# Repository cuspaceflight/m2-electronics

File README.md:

# Martlet 2 Flight Computers

This repository contains the schematics, PCB designs and firmware for the
various electronic systems onboard Martlet 2.

## M2FC: Flight Computer
This PCB records sensor data to onboard storage and determines when to fire
pyrotechnic channels for staging and parachute release.

## M2R: Radio
This PCB receives GPS signals and transmits rocket telemetry (lat, lng, alt, 
max alt) over a satellite radio and 70cm radio link.

## Radio Link M2RL
Communicate between two M2FCs

## Firmware
### ChibiOS Instructions

```bash
$ git submodule update --init
$ cd ChibiOS/ext
$ unzip fatfs-0.9-patched.zip
$ cd ../os/various/fatfs_bindings
$ sed -i '/extern SDCDriver SDCD1;/d' fatfs_diskio.c
```

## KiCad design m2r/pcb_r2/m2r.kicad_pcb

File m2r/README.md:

# Martlet 2 Radio Board

This PCB transmits rocket telemetry (lat, lng, alt, max alt) over a satellite
radio and 70cm radio link.

The satellite radio uses a RockBLOCK Iridium modem. The 70cm link will use an
NTX2b from Radiometrix with a standard 1/4 wave antenna, in a similar setup to
the usual HAB case.

There's some possibility for clever radio modes and coding to be used, but it
will depend on how much time is available.

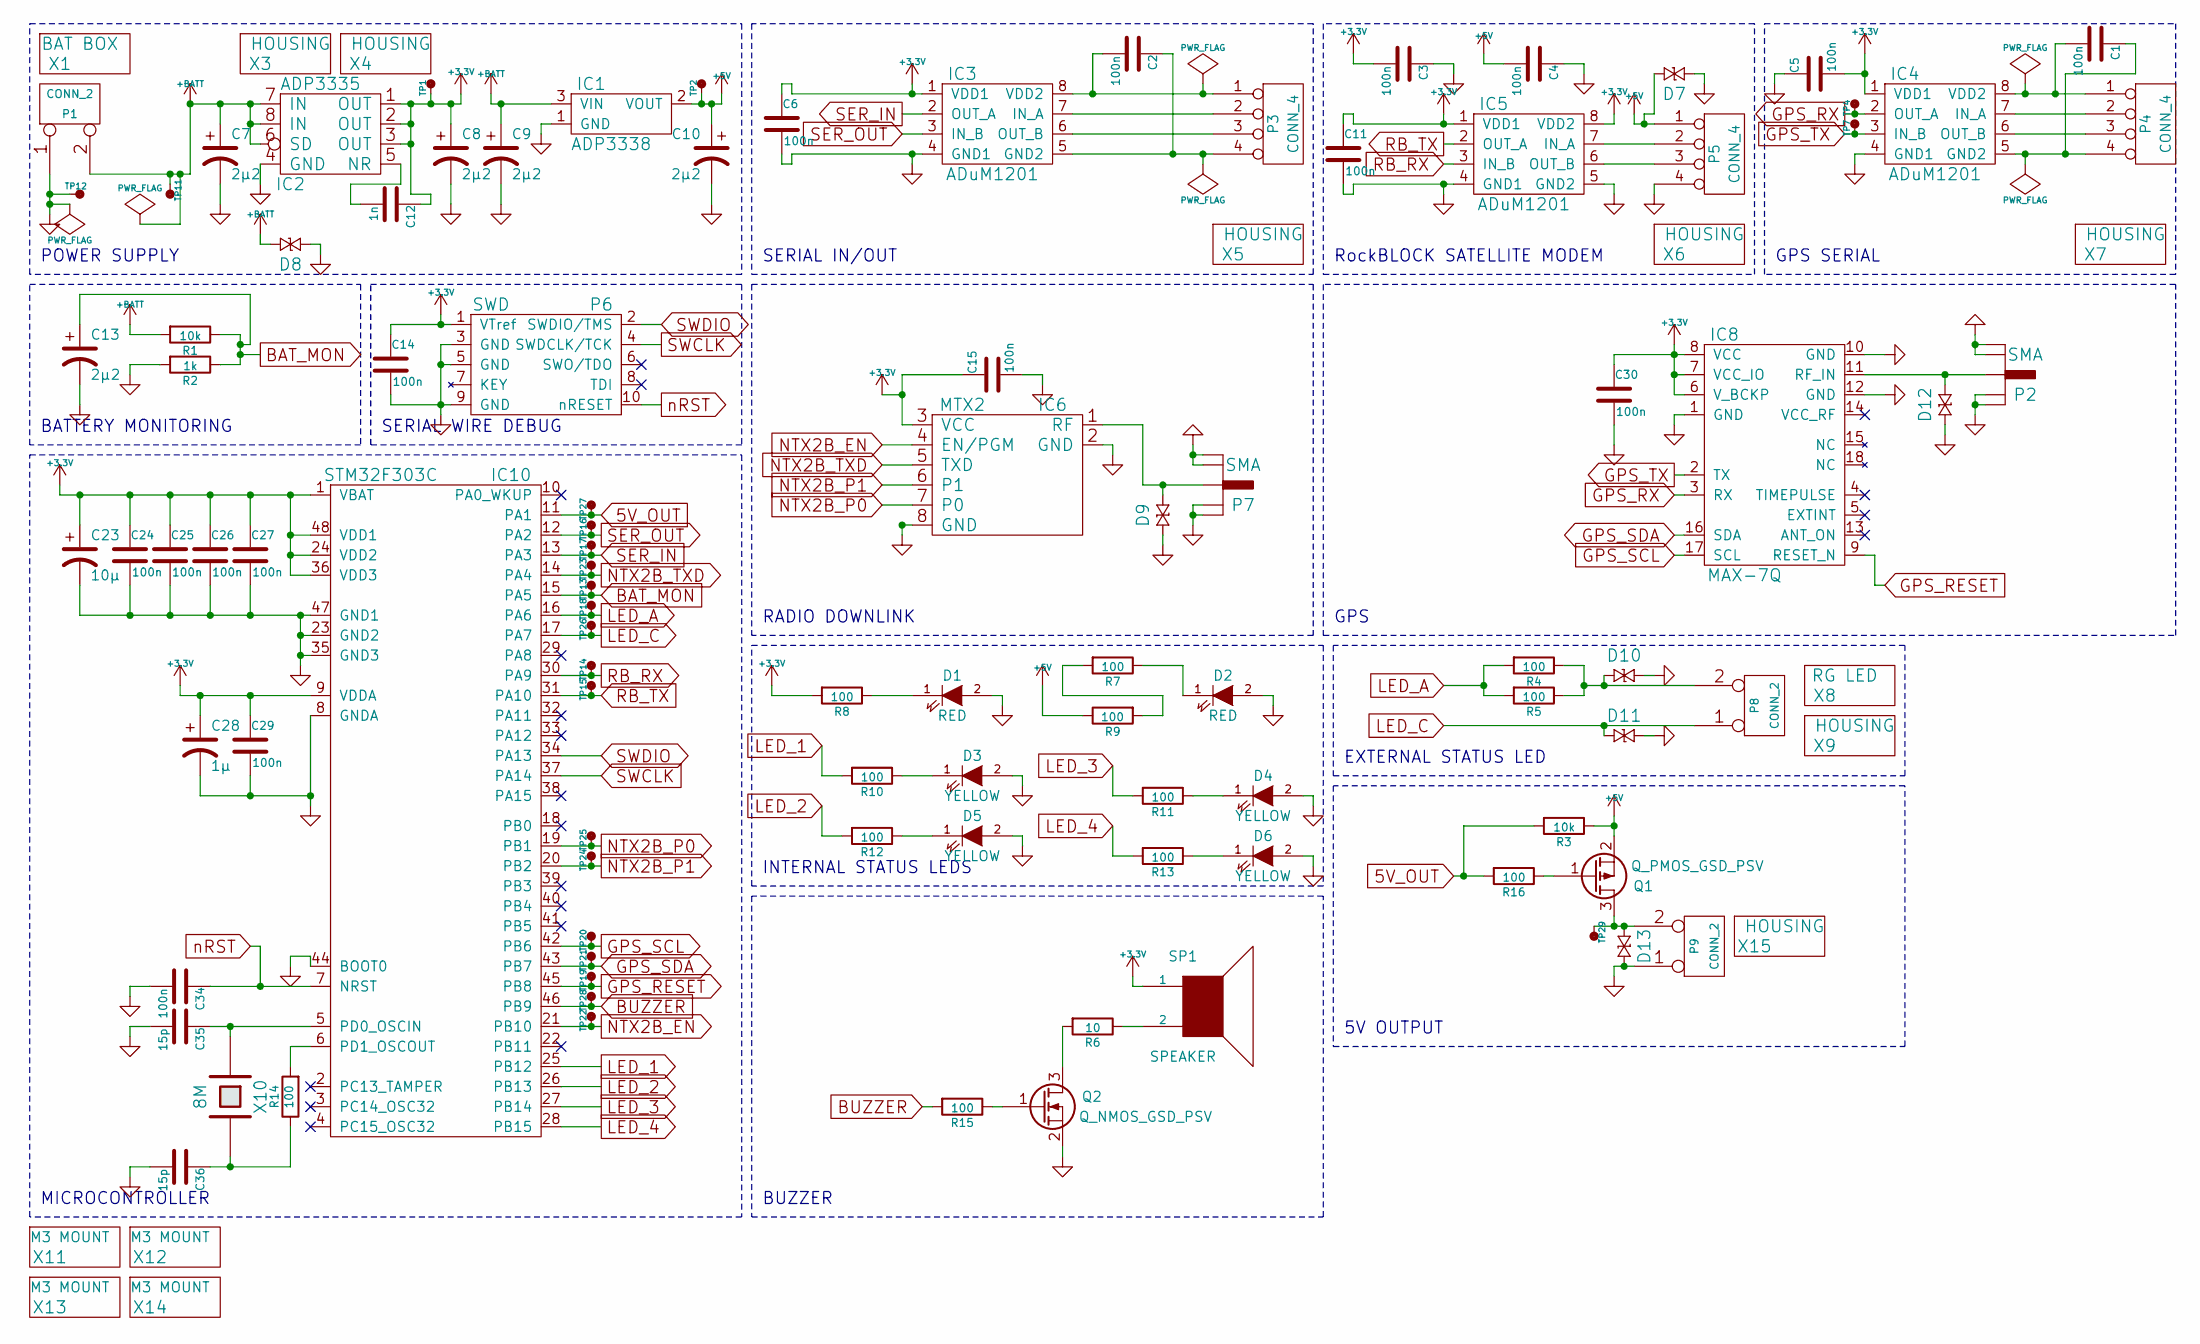
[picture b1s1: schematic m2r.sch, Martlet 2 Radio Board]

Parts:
C1, C2, C3, C4, C5, C6, C11, C14, C15, C24, C25, C26, C27, C29, C30, C34: 100n; C0603; Farnell 1759037
C7, C8, C9, C10, C13: 2µ2; C0603; Farnell 2320817
C12: 1n; C0603; Farnell 1759088
C23: 10µ; C0603; Farnell 2333026
C28: 1µ; C0603; Farnell 1658211
C35, C36: 15p; C0603; Farnell 1759055
D1, D2: RED; LED0603; Farnell 2290329
D3, D4, D5, D6: YELLOW; LED0603; Farnell 2290330
D7, D8, D9, D10, D11, D12, D13: CGA0402MLC-12G; R0402; Farnell 2368169
IC1: ADP3338; SOT223; Farnell 1651284
IC2: ADP3335; MSOP8; Farnell 2067775
IC3, IC4, IC5: ADuM1201; SOIC8; Farnell 1078200
IC6: MTX2
IC8: MAX-7Q
IC10: STM32F303C; LQFP48; Farnell 2333361
P1, P8, P9: CONN_2; S02B-PASK-2; Farnell 1830747
P2, P7: SMA; SMA-142-0701-801; Farnell 1608592
P3, P4, P5: CONN_4; S04B-PASK-2
P6: SWD; FTSH-105-01-F-D-K; Farnell 2308436
Q1: Q_PMOS_GSD_PSV; SOT-23; Farnell 1894738
Q2: Q_NMOS_GSD_PSV; SOT-23; Farnell 1510761
R1, R3: 10k; R0603; Farnell 2332016
R2: 1k; R0603; Farnell 2331727
R4, R5, R7, R8, R9, R10, R11, R12, R13, R14, R15, R16: 100; R0603; Farnell 2331989
R6: 10; R0603; Farnell 2331975
SP1: SPEAKER; ABI-042-RC; Farnell 1827949
TP1, TP2, TP4, TP7, TP11, TP12, TP13, TP14, TP15, TP16, TP17, TP18, TP19, TP20, TP21, TP22, TP23, TP24, TP25, TP26, TP27, TP28, TP29: TESTPAD
X1: BAT BOX; Farnell BT01732
X3, X4, X9, X15: HOUSING; Farnell 1830726
X5, X6, X7: HOUSING; Farnell 1830729
X8: RG LED; Farnell 1142488
X10: 8M; XTAL50x32; Farnell 2101329
X11, X12, X13, X14: M3 MOUNT; M3_MOUNT

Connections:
5V_OUT: IC10.11 (PA1), R3.2, R16.2, TP27.1
+3V3: C3.2, C5.2, C6.1, C8.1, C11.1, C12.1, C14.1, C15.1, C23.1, C24.1, C25.1, C26.1, C27.1, C28.1, C29.1, C30.1, IC2.1 (OUT), IC2.2 (OUT), IC2.3 (OUT), IC3.1 (VDD1), IC4.1 (VDD1), IC5.1 (VDD1), IC5.8 (VDD2), IC6.3 (VCC), IC8.6 (V_BCKP), IC8.7 (VCC_IO), IC8.8 (VCC), IC10.1 (VBAT), IC10.9 (VDDA), IC10.24 (VDD2), IC10.36 (VDD3), IC10.48 (VDD1), P6.1 (VTref), R8.2, SP1.1, TP1.1
+5V: C4.2, C10.1, D7.1, IC1.2 (VOUT), P5.1, Q1.2 (S), R3.1, R9.1, TP2.1
+BATT: C7.1, C9.1, D8.1, IC1.3 (VIN), IC2.6 (SD), IC2.7 (IN), IC2.8 (IN), P1.2 (PM), R1.2, TP11.1
BAT_MON: C13.1, IC10.15 (PA5), R1.1, R2.1, TP13.1
BUZZER: IC10.46 (PB9), R15.2, TP28.1
GND: C3.1, C4.1, C5.1, C6.2, C7.2, C8.2, C9.2, C10.2, C11.2, C13.2, C14.2, C15.2, C23.2, C24.2, C25.2, C26.2, C27.2, C28.2, C29.2, C30.2, C34.2, C35.2, C36.2, D1.2 (A), D2.2 (A), D3.2 (A), D4.2 (A), D5.2 (A), D6.2 (A), D7.2, D8.2, D9.2, D10.1, D11.1, D12.2, D13.1, IC1.1 (GND), IC2.4 (GND), IC3.4 (GND1), IC4.4 (GND1), IC5.4 (GND1), IC5.5 (GND2), IC6.2 (GND), IC6.8 (GND), IC8.1 (GND), IC8.10 (GND), IC8.12 (GND), IC10.8 (GNDA), IC10.23 (GND2), IC10.35 (GND3), IC10.44 (BOOT0), IC10.47 (GND1), P1.1, P2.2 (GND), P2.3 (GND), P2.4 (GND), P2.5 (GND), P5.4, P6.3 (GND), P6.5 (GND), P6.9 (GND), P7.2 (GND), P7.3 (GND), P7.4 (GND), P7.5 (GND), P9.1, Q2.2 (S), R2.2, TP12.1
GPS_RESET: IC8.9 (RESET_N), IC10.45 (PB8), TP19.1
GPS_RX: IC4.2 (OUT_A), IC8.3 (RX), TP4.1
GPS_SCL: IC8.17 (SCL), IC10.42 (PB6), TP20.1
GPS_SDA: IC8.16 (SDA), IC10.43 (PB7), TP21.1
GPS_TX: IC4.3 (IN_B), IC8.2 (TX), TP7.1
LED_1: IC10.25 (PB12), R10.2
LED_2: IC10.26 (PB13), R12.2
LED_3: IC10.27 (PB14), R11.2
LED_4: IC10.28 (PB15), R13.2
LED_A: IC10.16 (PA6), R4.2, R5.2, TP18.1
LED_C: D11.2, IC10.17 (PA7), P8.1, TP26.1
NTX2B_EN: IC6.4 (EN/PGM), IC10.21 (PB10), TP22.1
NTX2B_P0: IC6.7 (P0), IC10.19 (PB1), TP25.1
NTX2B_P1: IC6.6 (P1), IC10.20 (PB2), TP24.1
NTX2B_TXD: IC6.5 (TXD), IC10.14 (PA4), TP23.1
unnamed: C1.1, IC4.5 (GND2), P4.4
unnamed: C1.2, IC4.8 (VDD2), P4.1
unnamed: C2.1, IC3.5 (GND2), P3.4
unnamed: C2.2, IC3.8 (VDD2), P3.1
unnamed: C12.2, IC2.5 (NR)
unnamed: C35.1, IC10.5 (PD0_OSCIN), X10.1
unnamed: C36.1, R14.1, X10.2
unnamed: D1.1 (K), R8.1
unnamed: D2.1 (K), R7.1
unnamed: D3.1 (K), R10.1
unnamed: D4.1 (K), R11.1
unnamed: D5.1 (K), R12.1
unnamed: D6.1 (K), R13.1
unnamed: D9.1, IC6.1 (RF), P7.1 (RF)
unnamed: D10.2, P8.2 (PM), R4.1, R5.1
unnamed: D12.1, IC8.11 (RF_IN), P2.1 (RF)
unnamed: D13.2, P9.2 (PM), Q1.3 (D), TP29.1
unnamed: IC3.6 (OUT_B), P3.3
unnamed: IC3.7 (IN_A), P3.2
unnamed: IC4.6 (OUT_B), P4.3
unnamed: IC4.7 (IN_A), P4.2
unnamed: IC5.6 (OUT_B), P5.3
unnamed: IC5.7 (IN_A), P5.2
unnamed: IC10.6 (PD1_OSCOUT), R14.2
unnamed: Q1.1 (G), R16.1
unnamed: Q2.1 (G), R15.1
unnamed: Q2.3 (D), R6.2
unnamed: R6.1, SP1.2
unnamed: R7.2, R9.2
RB_RX: IC5.3 (IN_B), IC10.30 (PA9), TP14.1
RB_TX: IC5.2 (OUT_A), IC10.31 (PA10), TP15.1
SER_IN: IC3.2 (OUT_A), IC10.13 (PA3), TP17.1
SER_OUT: IC3.3 (IN_B), IC10.12 (PA2), TP16.1
SWCLK: IC10.37 (PA14), P6.4 (SWDCLK/TCK)
SWDIO: IC10.34 (PA13), P6.2 (SWDIO/TMS)
nRST: C34.1, IC10.7 (NRST), P6.10 (nRESET)

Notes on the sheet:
POWER SUPPLY
BATTERY MONITORING
SERIAL WIRE DEBUG
SERIAL IN/OUT
RockBLOCK SATELLITE MODEM
RADIO DOWNLINK
GPS
MICROCONTROLLER
EXTERNAL STATUS LED
INTERNAL STATUS LEDS
GPS SERIAL
BUZZER
5V OUTPUT

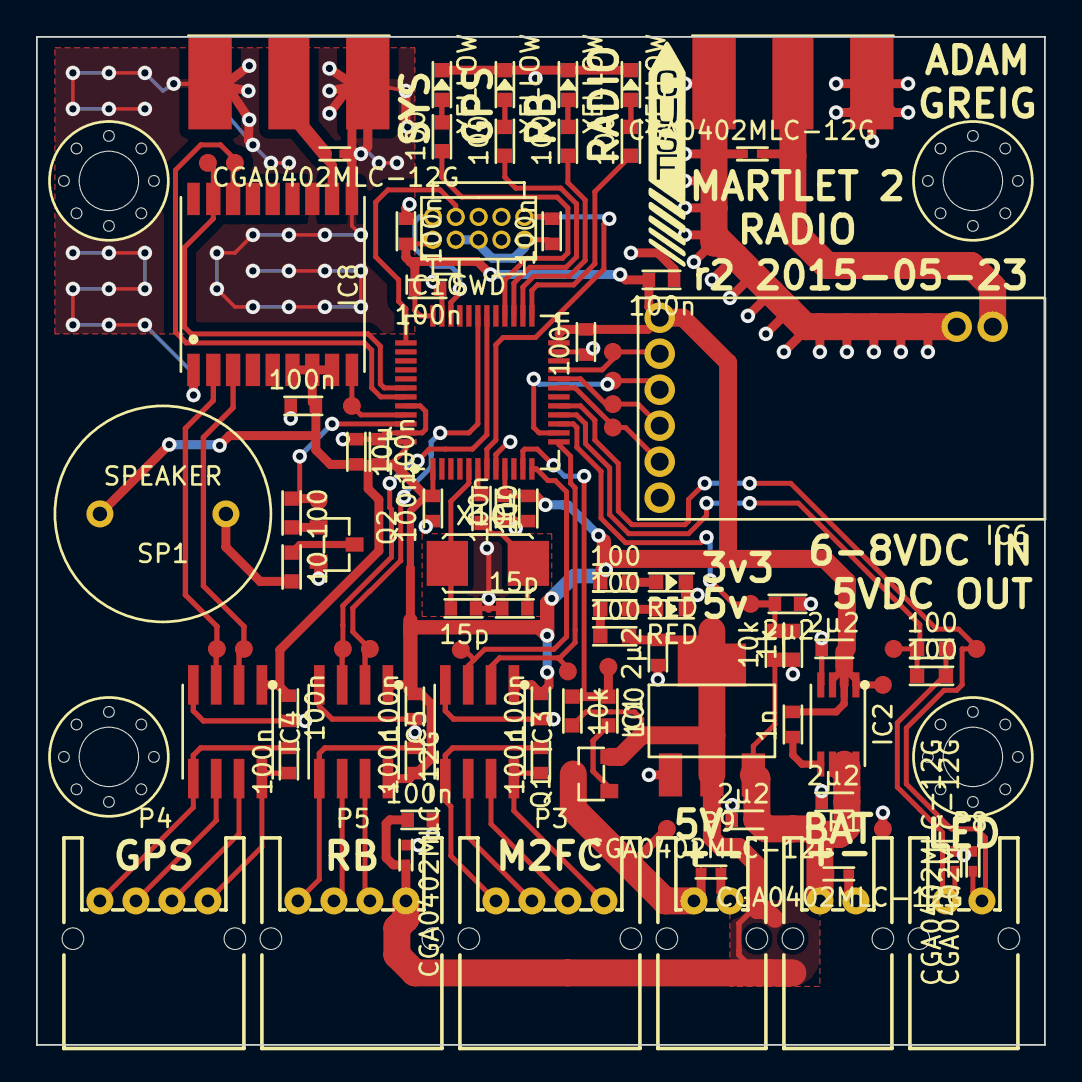
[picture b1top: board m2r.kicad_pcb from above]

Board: 2 copper layers, 56.0 x 56.0 mm, 103 parts (0 on the bottom side), 58 nets.

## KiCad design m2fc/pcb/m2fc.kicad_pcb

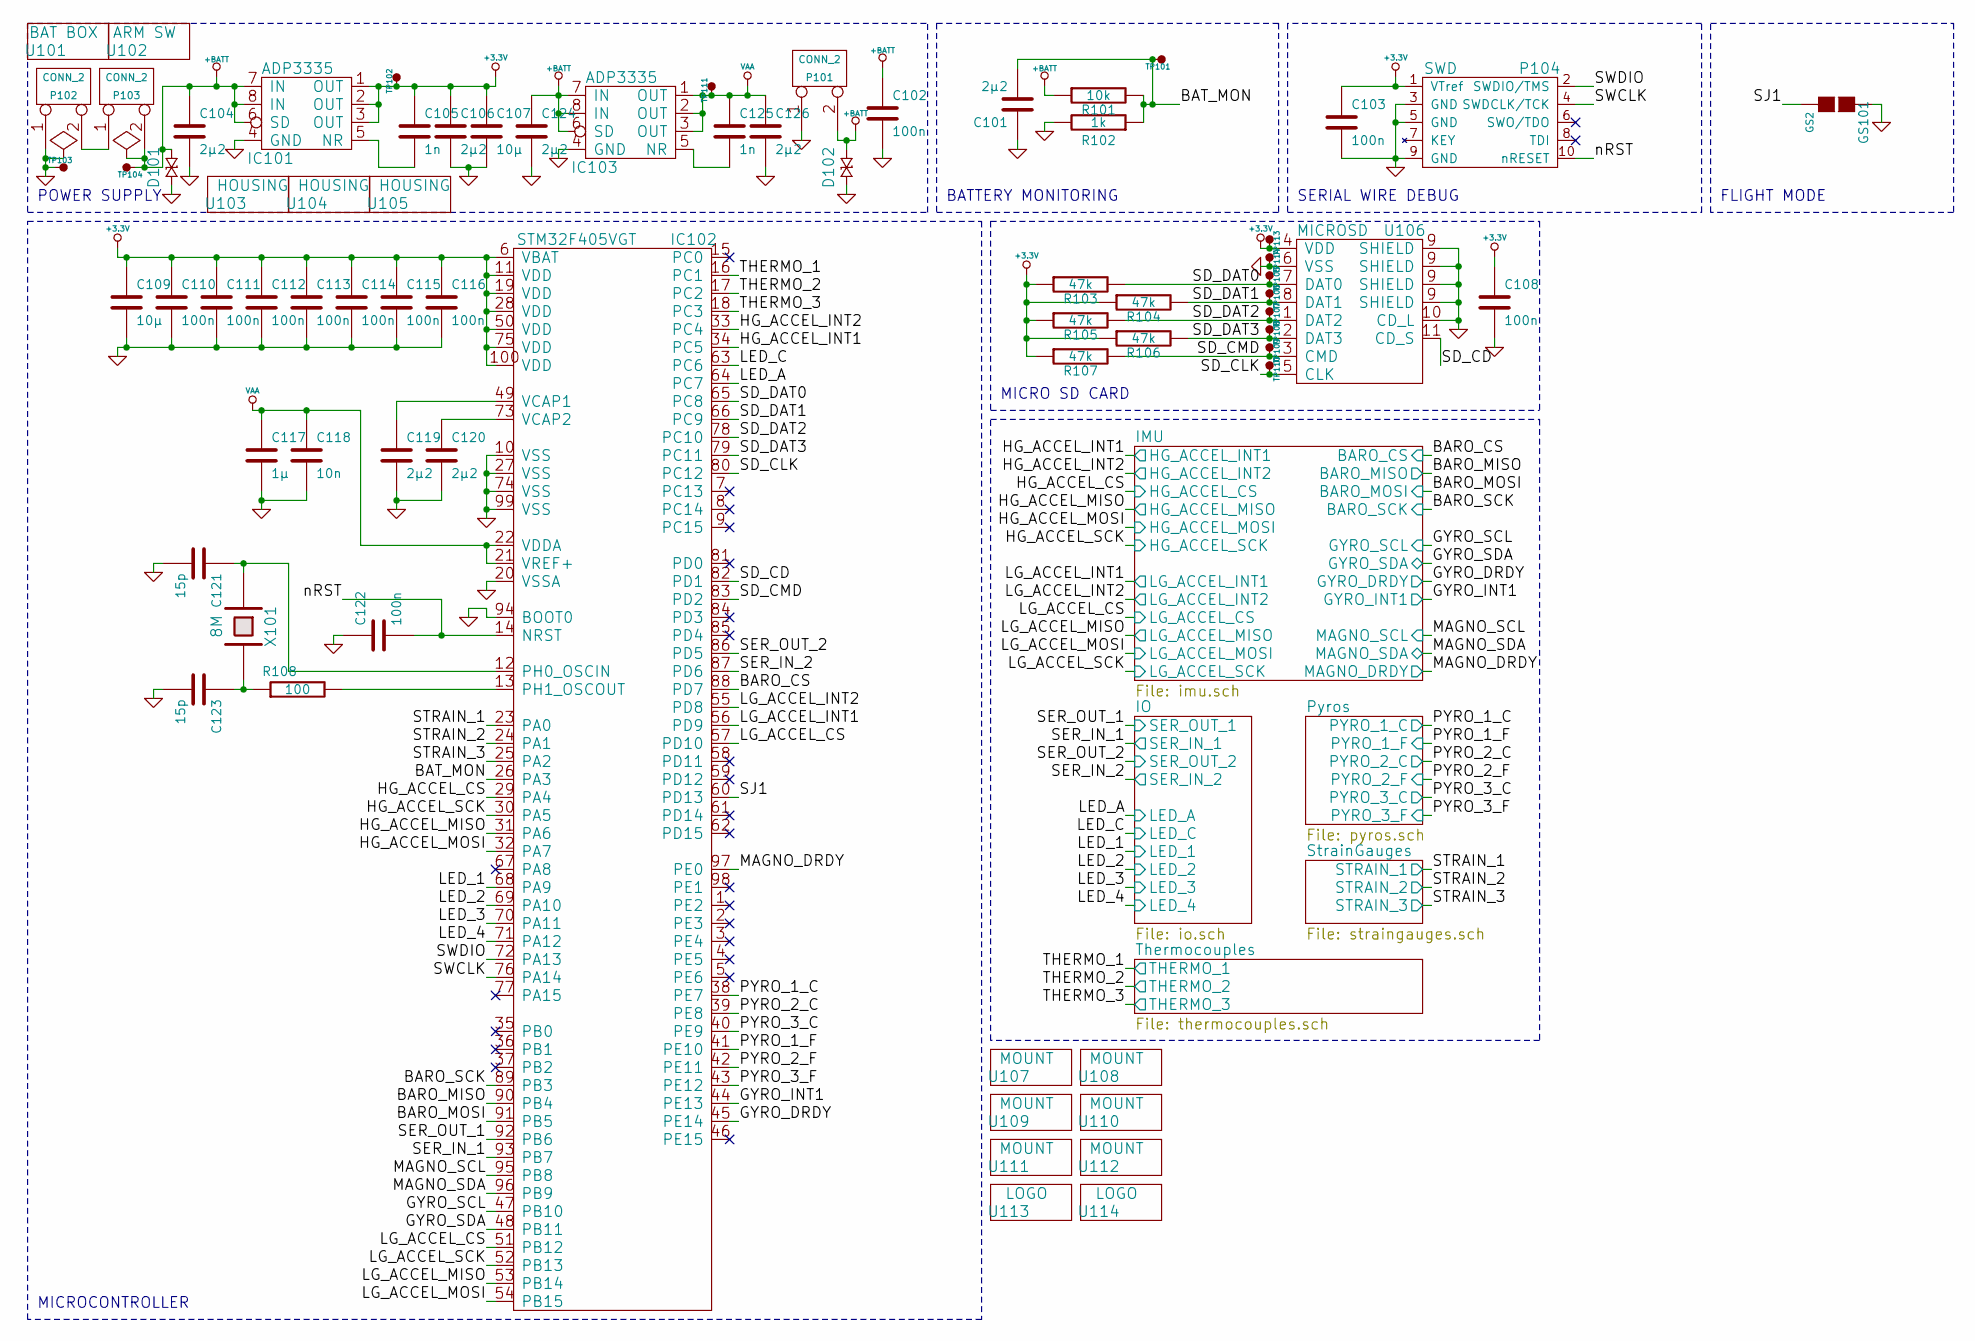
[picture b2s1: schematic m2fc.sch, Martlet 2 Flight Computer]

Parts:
C101, C104, C106, C119, C120, C124, C126: 2µ2; C0603; Farnell 2320817
C102, C103, C108, C110, C111, C112, C113, C114, C115, C116, C122: 100n; C0603; Farnell 1759037
C105, C125: 1n; C0603; Farnell 1414605
C107, C109: 10µ; C0603; Farnell 2211164
C117: 1µ; C0603; Farnell 2346895
C118: 10n; C0603; Farnell 2112704
C121, C123: 15p; C0603; Farnell 1759055
D101, D102: CGA0402MLC-12G; R0402; Farnell 2368169
GS101: GS2
IC101, IC103: ADP3335; MSOP8; Farnell 2067775
IC102: STM32F405VGT; LQFP100; Farnell 2393648
P101, P102, P103: CONN_2; S02B-PASK-2; Farnell 1830747
P104: SWD; FTSH-105-01-F-D-K; Farnell 1667759
R101: 10k; R0603; Farnell 2332016
R102: 1k; R0603; Farnell 2116678
R103, R104, R105, R106, R107: 47k; R0603; Farnell 2332025
R108: 100; R0603; Farnell 2331989
TP101, TP102, TP103, TP104, TP105, TP106, TP107, TP108, TP109, TP110, TP111, TP113, TP114: TESTPAD
U101: BAT BOX; Farnell BT01732
U102: ARM SW; Farnell SW04244
U103, U104, U105: HOUSING; Farnell 1830726
U106: MICROSD; Farnell 2334075
U107, U108, U109, U110, U111, U112: MOUNT; M3_MOUNT
U113: LOGO; cusf_logo_full
U114: LOGO; cusf_logo_small
X101: 8M; XTAL50x32; Farnell 2101329

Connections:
+3.3V: C103.1, C105.1, C106.1, C107.1, C108.1, C109.1, C110.1, C111.1, C112.1, C113.1, C114.1, C115.1, C116.1, IC101.1 (OUT), IC101.2 (OUT), IC101.3 (OUT), IC102.6 (VBAT), IC102.11 (VDD), IC102.19 (VDD), IC102.28 (VDD), IC102.50 (VDD), IC102.75 (VDD), IC102.100 (VDD), P104.1 (VTref), R103.1, R104.1, R105.1, R106.1, R107.1, TP102.1, TP113.1, U106.4 (VDD); also elsewhere on the board
+BATT: C102.1, C104.1, C124.1, D101.1, D102.1, IC101.6 (SD), IC101.7 (IN), IC101.8 (IN), IC103.6 (SD), IC103.7 (IN), IC103.8 (IN), P101.2 (PM), P103.2 (PM), R101.1, TP104.1; also elsewhere on the board
/BAT_MON: C101.2, IC102.26 (PA3), R101.2, R102.1, TP101.1
/IMU/BARO_CS: IC102.88 (PD7); also elsewhere on the board
/IMU/BARO_MISO: IC102.90 (PB4); also elsewhere on the board
/IMU/BARO_MOSI: IC102.91 (PB5); also elsewhere on the board
/IMU/BARO_SCK: IC102.89 (PB3); also elsewhere on the board
/IMU/GYRO_DRDY: IC102.45 (PE14); also elsewhere on the board
/IMU/GYRO_INT1: IC102.44 (PE13); also elsewhere on the board
/IMU/GYRO_SCL: IC102.47 (PB10); also elsewhere on the board
/IMU/GYRO_SDA: IC102.48 (PB11); also elsewhere on the board
/IMU/HG_ACCEL_CS: IC102.29 (PA4); also elsewhere on the board
/IMU/HG_ACCEL_INT1: IC102.34 (PC5); also elsewhere on the board
/IMU/HG_ACCEL_INT2: IC102.33 (PC4); also elsewhere on the board
/IMU/HG_ACCEL_MISO: IC102.31 (PA6); also elsewhere on the board
/IMU/HG_ACCEL_MOSI: IC102.32 (PA7); also elsewhere on the board
/IMU/HG_ACCEL_SCK: IC102.30 (PA5); also elsewhere on the board
/IMU/LG_ACCEL_CS: IC102.51 (PB12), IC102.57 (PD10); also elsewhere on the board
/IMU/LG_ACCEL_INT1: IC102.56 (PD9); also elsewhere on the board
/IMU/LG_ACCEL_INT2: IC102.55 (PD8); also elsewhere on the board
/IMU/LG_ACCEL_MISO: IC102.53 (PB14); also elsewhere on the board
/IMU/LG_ACCEL_MOSI: IC102.54 (PB15); also elsewhere on the board
/IMU/LG_ACCEL_SCK: IC102.52 (PB13); also elsewhere on the board
/IMU/MAGNO_DRDY: IC102.97 (PE0); also elsewhere on the board
/IMU/MAGNO_SCL: IC102.95 (PB8); also elsewhere on the board
/IMU/MAGNO_SDA: IC102.96 (PB9); also elsewhere on the board
/IO/LED_1: IC102.68 (PA9); also elsewhere on the board
/IO/LED_2: IC102.69 (PA10); also elsewhere on the board
/IO/LED_3: IC102.70 (PA11); also elsewhere on the board
/IO/LED_4: IC102.71 (PA12); also elsewhere on the board
/IO/LED_A: IC102.64 (PC7); also elsewhere on the board
/IO/LED_C: IC102.63 (PC6); also elsewhere on the board
/IO/SER_IN_1: IC102.93 (PB7); also elsewhere on the board
/IO/SER_IN_2: IC102.87 (PD6); also elsewhere on the board
/IO/SER_OUT_1: IC102.92 (PB6); also elsewhere on the board
/IO/SER_OUT_2: IC102.86 (PD5); also elsewhere on the board
/Pyros/PYRO_1_C: IC102.38 (PE7); also elsewhere on the board
/Pyros/PYRO_1_F: IC102.41 (PE10); also elsewhere on the board
/Pyros/PYRO_2_C: IC102.39 (PE8); also elsewhere on the board
/Pyros/PYRO_2_F: IC102.42 (PE11); also elsewhere on the board
/Pyros/PYRO_3_C: IC102.40 (PE9); also elsewhere on the board
/Pyros/PYRO_3_F: IC102.43 (PE12); also elsewhere on the board
/SD_CD: IC102.82 (PD1), U106.11 (CD_S)
/SD_CLK: IC102.80 (PC12), TP110.1, U106.5 (CLK)
/SD_CMD: IC102.83 (PD2), R107.2, TP109.1, U106.3 (CMD)
/SD_DAT0: IC102.65 (PC8), R103.2, TP105.1, U106.7 (DAT0)
/SD_DAT1: IC102.66 (PC9), R104.2, TP106.1, U106.8 (DAT1)
/SD_DAT2: IC102.78 (PC10), R105.2, TP107.1, U106.1 (DAT2)
/SD_DAT3: IC102.79 (PC11), R106.2, TP108.1, U106.2 (DAT3)
/SJ1: GS101.2 (G2), IC102.60 (PD13)
/SWCLK: IC102.76 (PA14), P104.4 (SWDCLK/TCK)
/SWDIO: IC102.72 (PA13), P104.2 (SWDIO/TMS)
/StrainGauges/STRAIN_1: IC102.23 (PA0); also elsewhere on the board
/StrainGauges/STRAIN_2: IC102.24 (PA1); also elsewhere on the board
/StrainGauges/STRAIN_3: IC102.25 (PA2); also elsewhere on the board
/Thermocouples/THERMO_1: IC102.16 (PC1); also elsewhere on the board
/Thermocouples/THERMO_2: IC102.17 (PC2); also elsewhere on the board
/Thermocouples/THERMO_3: IC102.18 (PC3); also elsewhere on the board
/nRST: C122.2, IC102.14 (NRST), P104.10 (nRESET)
GND: C101.1, C102.2, C103.2, C104.2, C106.2, C107.2, C108.2, C109.2, C110.2, C111.2, C112.2, C113.2, C114.2, C115.2, C116.2, C117.2, C118.2, C119.2, C120.2, C121.2, C122.1, C123.2, C124.2, C126.2, D101.2, D102.2, GS101.1 (G1), IC101.4 (GND), IC102.10 (VSS), IC102.20 (VSSA), IC102.27 (VSS), IC102.74 (VSS), IC102.94 (BOOT0), IC102.99 (VSS), IC103.4 (GND), P101.1, P102.1, P104.3 (GND), P104.5 (GND), P104.9 (GND), R102.2, TP103.1, TP114.1, U106.6 (VSS), U106.9 (SHIELD), U106.10 (CD_L); also elsewhere on the board
unnamed: C105.2, IC101.5 (NR)
unnamed: C119.1, IC102.49 (VCAP1)
unnamed: C120.1, IC102.73 (VCAP2)
unnamed: C121.1, IC102.12 (PH0_OSCIN), X101.1
unnamed: C123.1, R108.1, X101.2
unnamed: C125.2, IC103.5 (NR)
unnamed: IC102.13 (PH1_OSCOUT), R108.2
unnamed: P102.2 (PM), P103.1
VAA: C117.1, C118.1, C125.1, C126.1, IC102.21 (VREF+), IC102.22 (VDDA), IC103.1 (OUT), IC103.2 (OUT), IC103.3 (OUT), TP111.1; also elsewhere on the board

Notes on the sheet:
MICROCONTROLLER
POWER SUPPLY
BATTERY MONITORING
SERIAL WIRE DEBUG
MICRO SD CARD
FLIGHT MODE

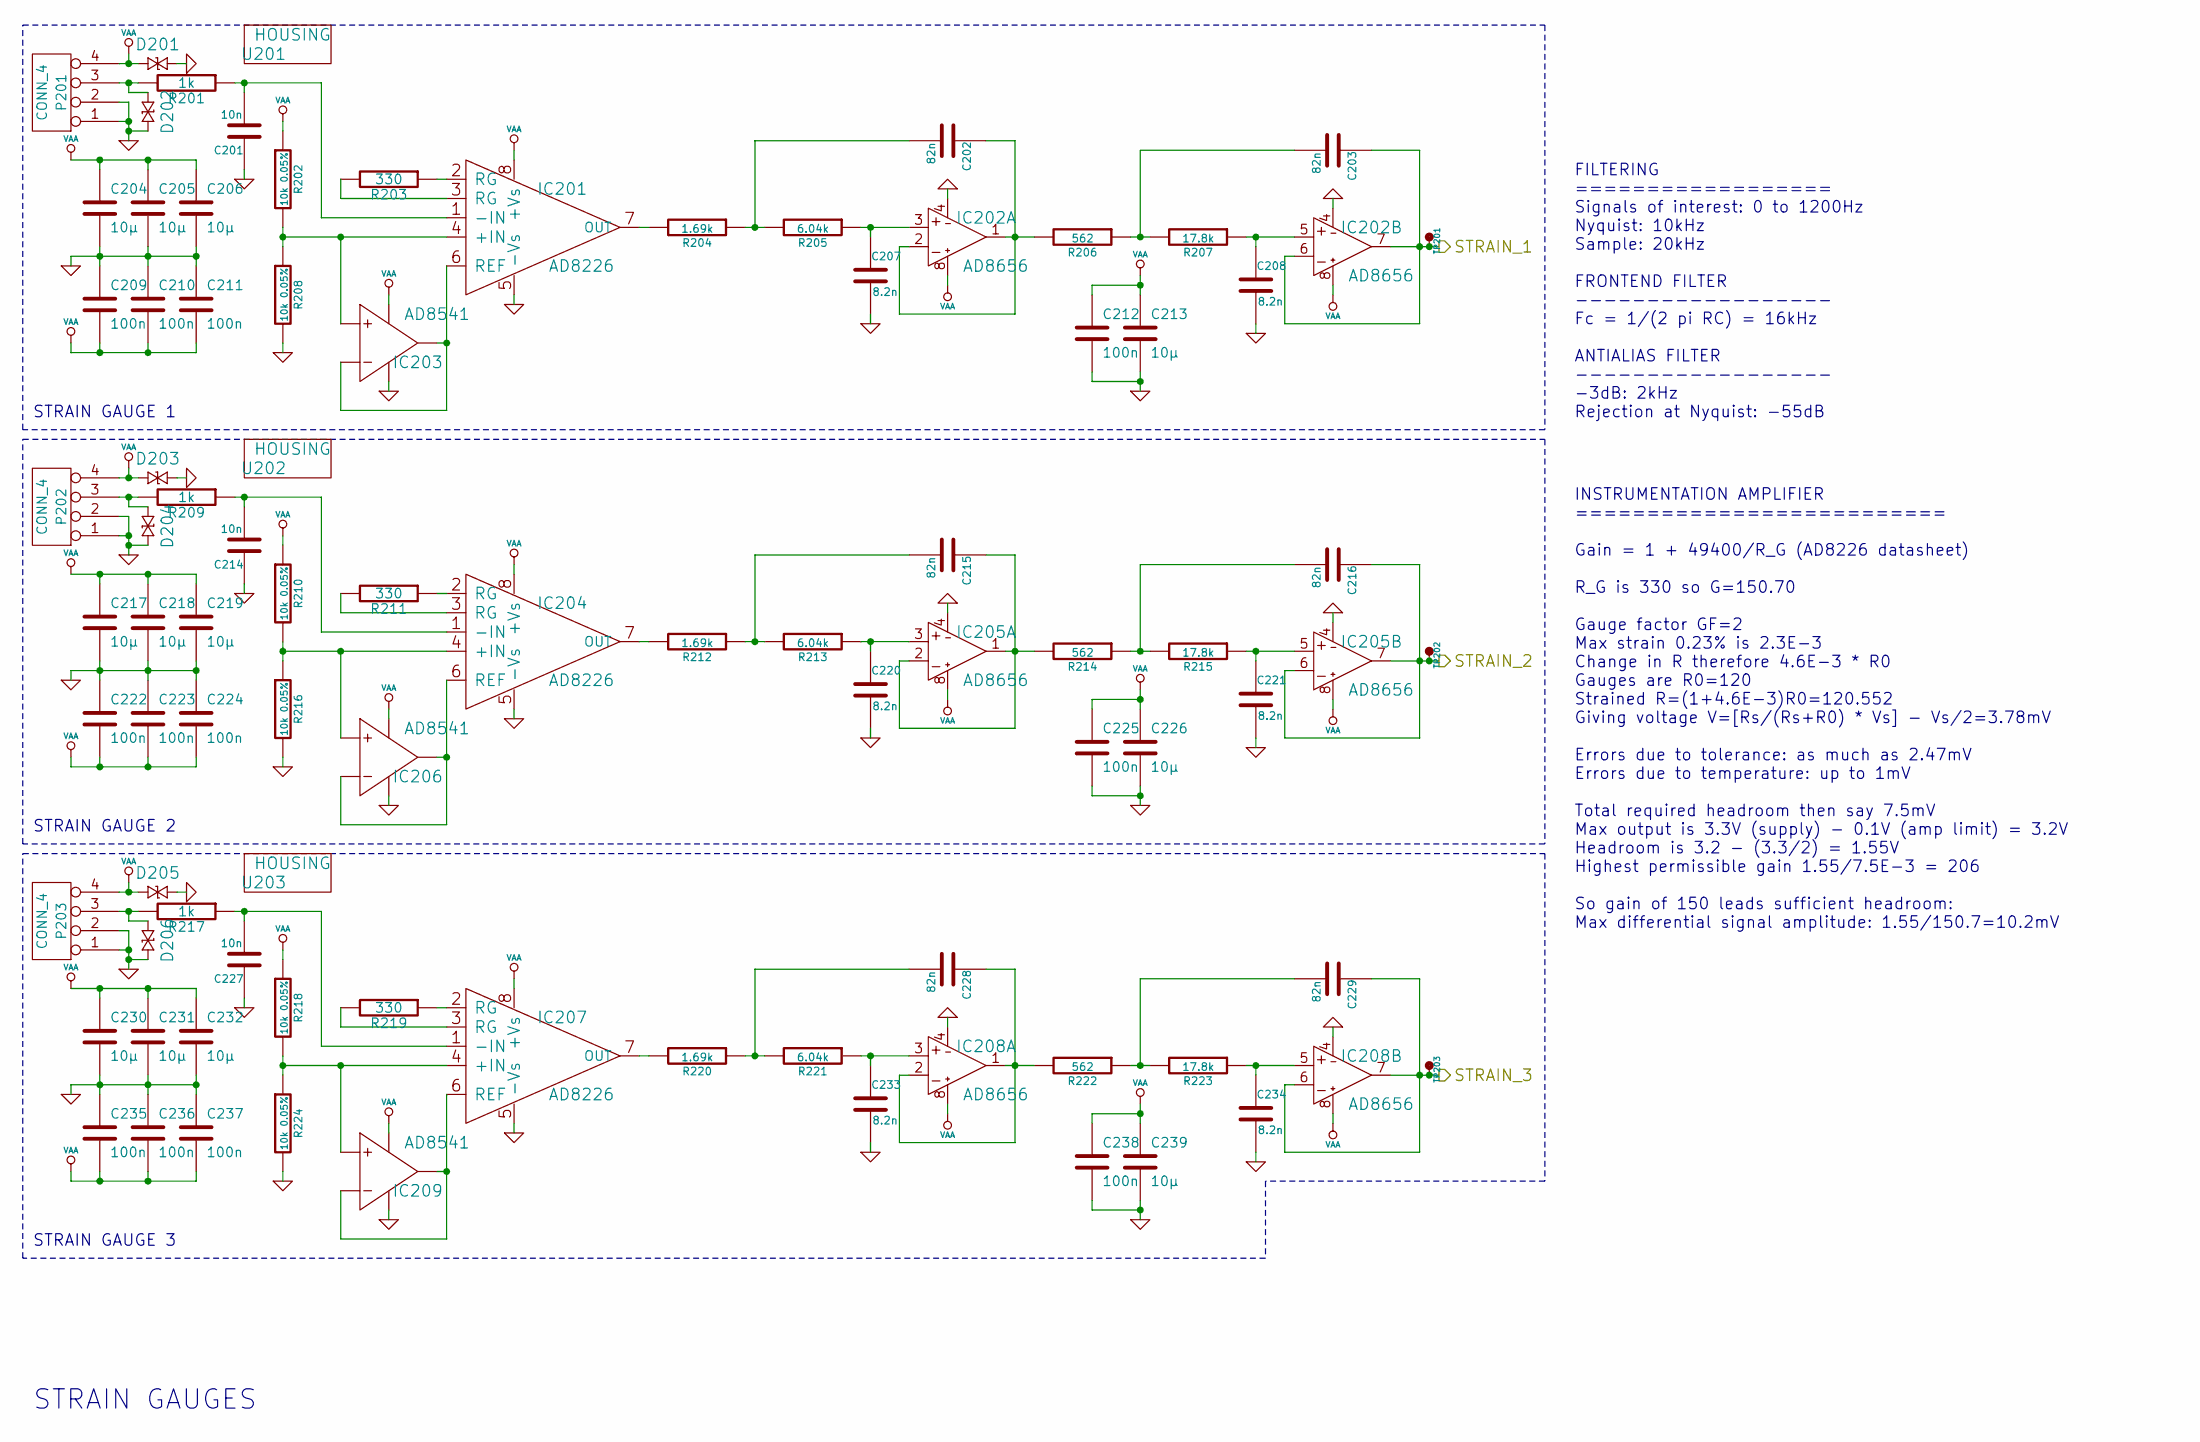
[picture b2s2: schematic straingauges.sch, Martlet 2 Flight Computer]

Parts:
C201, C214, C227: 10n; C0603; Farnell 2112704
C202, C203, C215, C216, C228, C229: 82n; C0603; Farnell 1865539
C204, C205, C206, C213, C217, C218, C219, C226, C230, C231, C232, C239: 10µ; C0603; Farnell 2211164
C207, C208, C220, C221, C233, C234: 8.2n; C0603; Farnell 2210859
C209, C210, C211, C212, C222, C223, C224, C225, C235, C236, C237, C238: 100n; C0603; Farnell 1759037
D201, D202, D203, D204, D205, D206: CGA0402MLC-12G; R0402; Farnell 2368169
IC201, IC204, IC207: AD8226; MSOP8; Farnell 1827359
IC202, IC205, IC208: AD8656; MSOP8; Farnell 1858055
IC203, IC206, IC209: AD8541; SC-70-5; Farnell 1837433
P201, P202, P203: CONN_4; S04B-PASK-2; Farnell 1830749
R201, R209, R217: 1k; R0603; Farnell 2116678
R202, R208, R210, R216, R218, R224: 10k 0.05%; R0603; Farnell 1877590
R203, R211, R219: 330; R0603; Farnell 1577599
R204, R212, R220: 1.69k; R0603; Farnell 2116702
R205, R213, R221: 6.04k; R0603; Farnell 2116761
R206, R214, R222: 562; R0603; Farnell 2116652
R207, R215, R223: 17.8k; R0603; Farnell 2116811
TP201, TP202, TP203: TESTPAD
U201, U202, U203: HOUSING; Farnell 1830729

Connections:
/StrainGauges/STRAIN_1: C203.1, IC202.6 (-IN), IC202.7 (OUT), TP201.1; also elsewhere on the board
/StrainGauges/STRAIN_2: C216.1, IC205.6 (-IN), IC205.7 (OUT), TP202.1; also elsewhere on the board
/StrainGauges/STRAIN_3: C229.1, IC208.6 (-IN), IC208.7 (OUT), TP203.1; also elsewhere on the board
GND: C201.1, C204.2, C205.2, C206.2, C207.2, C208.2, C209.1, C210.1, C211.1, C212.2, C213.2, C214.1, C217.2, C218.2, C219.2, C220.2, C221.2, C222.1, C223.1, C224.1, C225.2, C226.2, C227.1, C230.2, C231.2, C232.2, C233.2, C234.2, C235.1, C236.1, C237.1, C238.2, C239.2, D201.1, D202.1, D203.1, D204.1, D205.1, D206.1, IC201.5 (-Vs), IC202.4 (V-), IC203.2 (V-), IC204.5 (-Vs), IC205.4 (V-), IC206.2 (V-), IC207.5 (-Vs), IC208.4 (V-), IC209.2 (V-), P201.1, P201.2, P202.1, P202.2, P203.1, P203.2, R208.2, R216.2, R224.2; also elsewhere on the board
unnamed: C201.2, IC201.1 (-IN), R201.1
unnamed: C202.1, IC202.1 (OUT), IC202.2 (-IN), R206.2
unnamed: C202.2, R204.1, R205.2
unnamed: C203.2, R206.1, R207.2
unnamed: C207.1, IC202.3 (+IN), R205.1
unnamed: C208.1, IC202.5 (+IN), R207.1
unnamed: C214.2, IC204.1 (-IN), R209.1
unnamed: C215.1, IC205.1 (OUT), IC205.2 (-IN), R214.2
unnamed: C215.2, R212.1, R213.2
unnamed: C216.2, R214.1, R215.2
unnamed: C220.1, IC205.3 (+IN), R213.1
unnamed: C221.1, IC205.5 (+IN), R215.1
unnamed: C227.2, IC207.1 (-IN), R217.1
unnamed: C228.1, IC208.1 (OUT), IC208.2 (-IN), R222.2
unnamed: C228.2, R220.1, R221.2
unnamed: C229.2, R222.1, R223.2
unnamed: C233.1, IC208.3 (+IN), R221.1
unnamed: C234.1, IC208.5 (+IN), R223.1
unnamed: D202.2, P201.3, R201.2
unnamed: D204.2, P202.3, R209.2
unnamed: D206.2, P203.3, R217.2
unnamed: IC201.2 (RG), R203.1
unnamed: IC201.3 (RG), R203.2
unnamed: IC201.4 (+IN), IC203.3 (+), R202.2, R208.1
unnamed: IC201.6 (REF), IC203.1 (OUT), IC203.4 (-)
unnamed: IC201.7 (OUT), R204.2
unnamed: IC204.2 (RG), R211.1
unnamed: IC204.3 (RG), R211.2
unnamed: IC204.4 (+IN), IC206.3 (+), R210.2, R216.1
unnamed: IC204.6 (REF), IC206.1 (OUT), IC206.4 (-)
unnamed: IC204.7 (OUT), R212.2
unnamed: IC207.2 (RG), R219.1
unnamed: IC207.3 (RG), R219.2
unnamed: IC207.4 (+IN), IC209.3 (+), R218.2, R224.1
unnamed: IC207.6 (REF), IC209.1 (OUT), IC209.4 (-)
unnamed: IC207.7 (OUT), R220.2
VAA: C204.1, C205.1, C206.1, C209.2, C210.2, C211.2, C212.1, C213.1, C217.1, C218.1, C219.1, C222.2, C223.2, C224.2, C225.1, C226.1, C230.1, C231.1, C232.1, C235.2, C236.2, C237.2, C238.1, C239.1, D201.2, D203.2, D205.2, IC201.8 (+Vs), IC202.8 (V+), IC203.5 (V+), IC204.8 (+Vs), IC205.8 (V+), IC206.5 (V+), IC207.8 (+Vs), IC208.8 (V+), IC209.5 (V+), P201.4, P202.4, P203.4, R202.1, R210.1, R218.1; also elsewhere on the board

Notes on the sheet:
STRAIN GAUGE 1
FILTERING ================== Signals of interest: 0 to 1200Hz Nyquist: 10kHz Sample: 20kHz FRONTEND FILTER ------------------ Fc = 1/(2 pi RC) = 16kHz ANTIALIAS FILTER ------------------ -3dB: 2kHz Rejection at Nyquist: -55dB
STRAIN GAUGES
INSTRUMENTATION AMPLIFIER ========================== Gain = 1 + 49400/R_G (AD8226 datasheet) R_G is 330 so G=150.70 Gauge factor GF=2 Max strain 0.23% is 2.3E-3 Change in R therefore 4.6E-3 * R0 Gauges are R0=120 Strained R=(1+4.6E-3)R0=120.552 Giving voltage V=[Rs/(Rs+R0) * Vs] - Vs/2=3.78mV Error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
STRAIN GAUGE 2
STRAIN GAUGE 3
